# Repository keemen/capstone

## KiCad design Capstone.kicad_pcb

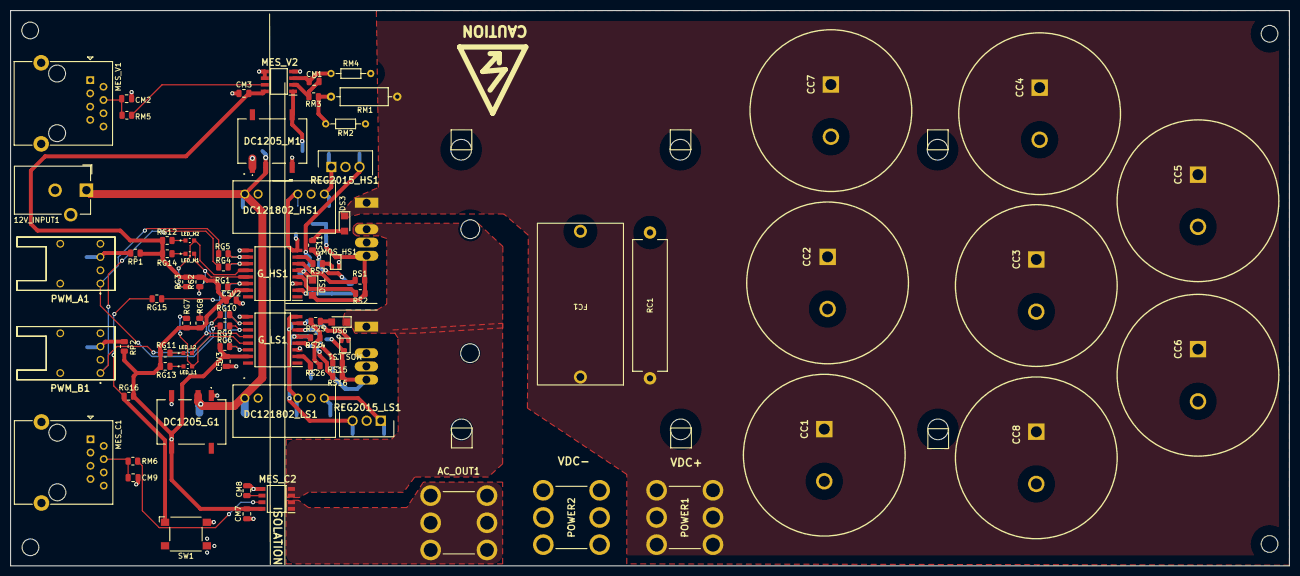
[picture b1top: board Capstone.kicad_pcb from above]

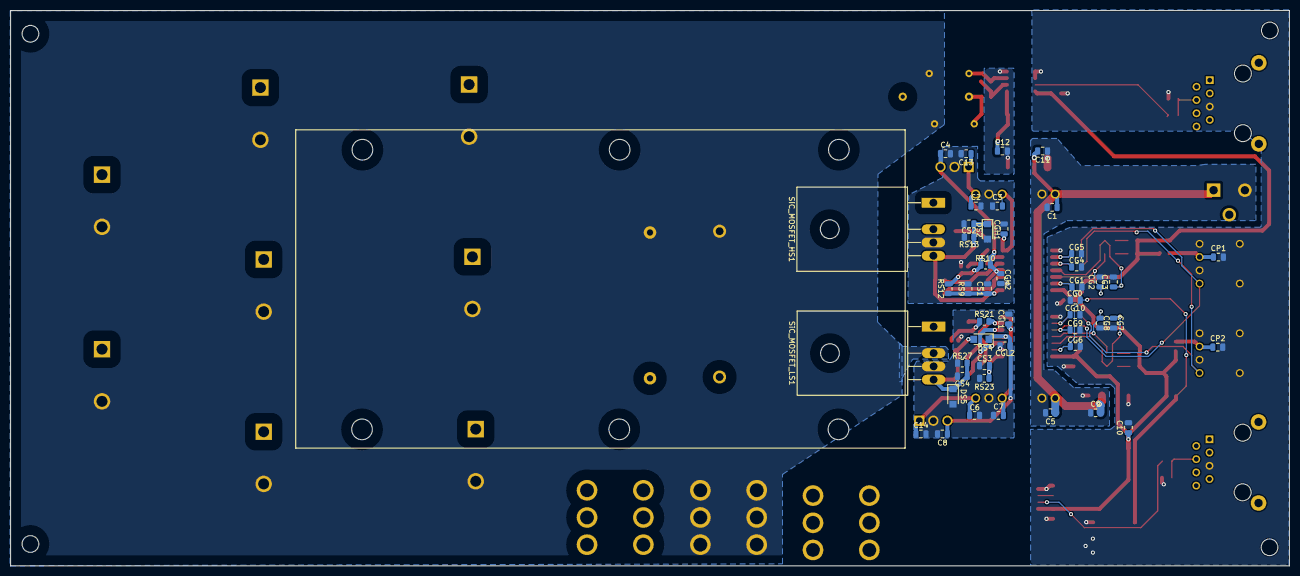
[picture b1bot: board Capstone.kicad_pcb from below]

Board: 2 copper layers, 245.1 x 106.4 mm, 126 parts (47 on the bottom side), 60 nets.

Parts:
12V_INPUT1: Barrel_Jack_FC681465P; BarrelJack_CUI_PJ-102AH_Horizontal
AC_OUT1: 8196
C1, C2, C3, C5, C6, C7, C10, C12: 10uF; C_0805_2012Metric
C4, C8: 0.1uF; C_0805_2012Metric
C5V2, C5V3: 100nF; C_0805_2012Metric
C9, C11: 2.2uF; C_0805_2012Metric
C13, C14: 0.33uF; C_0805_2012Metric
CC1, CC2, CC3, CC4, CC5, CC6, CC7, CC8: 381LX; CAPPRD1000W190D3100H3700
CG0: 16nF; C_0805_2012Metric
CG1, CG2, CG3, CG4, CG5, CG6, CG7, CG8, CG9, CG10: 100pF; C_0805_2012Metric
CGH1, CGH2: 10uF; C_0805_2012Metric
CGL1, CGL2: 10uF; C_0805_2012Metric
CM1: 10nF; C_0805_2012Metric
CM2: 40pF; C_0805_2012Metric
CM3: 100nF; C_0805_2012Metric
CM7: 1uF; C_0805_2012Metric
CM8: 1nF; C_0805_2012Metric
CM9: 100pF; C_0805_2012Metric
CP1, CP2: 0.1uF; C_0805_2012Metric
CS1, CS3: 55pF; C_0805_2012Metric
CS2, CS4: 4.7nF; C_0805_2012Metric
DC1205_G1, DC1205_M1: PDSE2-S24-S24-M; PDSE2S24S24M
DC121802_HS1, DC121802_LS1: MGJ2D121802SC; MGJ2D_7-PIN-SIP
DS1, DS2: SD; D_SMF
DS3, DS4, DS5, DS6: D; D_SMF
FC1: 106MMR250K
G_HS1: UCC21732DW; SOIC127P1030X265-16N
G_LS1: UCC21732DW; SOIC127P1030X265-16N
LED_H1, LED_H2: LED; LED_SML-D12V1WT86
LED_L1, LED_L2: LED; LED_SML-D12V1WT86
MES_C1: RJ45; RJ45_Ninigi_GE
MES_C2: ACHS-7124-000E
MES_V1: RJ45; RJ45_Ninigi_GE
MES_V2: SI8921BB-IS; SI8921
MOS_HS1: 2N7002KW-AU
MOS_LS1: 2N7002KW-AU
POWER1, POWER2: 8196
PWM_A1: AFBR-1528CZ; AFBR1528CZ
PWM_B1: AFBR-1528CZ; AFBR1528CZ
RC1: 20k; R_Axial_Power_L25.0mm_W6.4mm_P27.94mm
REG2015_HS1, REG2015_LS1: L78M15ABV; TO270P460X1020X2008-3P
RG1, RG2, RG3, RG6, RG7, RG8: 10k; R_0805_2012Metric
RG4, RG5, RG9, RG10, RG15: 100; R_0805_2012Metric
RG11, RG12, RG13, RG14: 200; R_0805_2012Metric
RG16: 5k; R_0805_2012Metric
RM1: 100k; R_Axial_DIN0309_L9.0mm_D3.2mm_P12.70mm_Horizontal
RM2, RM4: 20; R_Axial_DIN0204_L3.6mm_D1.6mm_P7.62mm_Horizontal
RM3: 20; R_0805_2012Metric
RM5: 10k; R_0805_2012Metric
RM6: 100; R_0805_2012Metric
RP1, RP2: 2.7; R_0805_2012Metric
RS1, RS2, RS15, RS16: 4.7; R_0805_2012Metric
RS7, RS21: 2; R_0805_2012Metric
RS9, RS23: 732; R_0805_2012Metric
RS10, RS24: 11.8k; R_0805_2012Metric
RS11, RS25: 33; R_0805_2012Metric
RS12, RS26: 3k; R_0805_2012Metric
RS13, RS27: 5k; R_0805_2012Metric
SW1: SW_Push; SW_SPST_Omron_B3FS-105xP
SiC_MOSFET_HS1: C3M0120065K; TO-247-4_Horizontal_TabUp
SiC_MOSFET_LS1: C3M0120065K; TO-247-4_Horizontal_TabUp

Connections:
/Gate_driver/5V_DC: C5V2.1, C5V3.1, C10.1, CM3.2, CM7.2, DC1205_G1.5 (+VO), G_HS1.15 (VCC), G_LS1.15 (VCC), MES_C2.8 (VDD), MES_V2.8 (VDDB), RG1.2, RG2.2, RG3.2, RG6.2, RG7.2, RG8.2, RG11.1, RG12.1, RG13.1, RG14.1, RG16.2, RP1.1, RP2.1
/Gate_driver/-2.5VDC_HS: C3.2, CGH1.1, DC121802_HS1.5 (-VOUT), G_HS1.8 (VEE)
/Gate_driver/-2.5VDC_LS: C7.2, CGL1.1, DC121802_LS1.5 (-VOUT), G_LS1.8 (VEE)
/Gate_driver/CLMPE_HS: G_HS1.7 (CLMPE), RS7.2
/Gate_driver/CLMPE_LS: G_LS1.7 (CLMPE), RS21.2
/Gate_driver/FLT_HS: CG2.1, G_HS1.13 (~FLT), LED_H1.1 (K), RG2.1
/Gate_driver/FLT_LS: CG7.1, G_LS1.13 (~FLT), LED_L1.1 (K), RG7.1
/Gate_driver/GND5V_G: C5V2.2, C5V3.2, C10.2, CG0.2, CG1.2, CG2.2, CG3.2, CG4.2, CG5.2, CG6.2, CG7.2, CG8.2, CG9.2, CG10.2, CM2.2, CM3.1, CM7.1, CM8.1, CM9.1, CP1.2, CP2.2, DC1205_G1.4 (0V), G_HS1.9 (GND), G_LS1.9 (GND), MES_C1.5, MES_C2.5 (GND), MES_V1.5, MES_V2.5 (GNDB), MES_V2.6 (AON), PWM_A1.2 (K), PWM_A1.4 (PIN_2), PWM_A1.5 (HOUSING_PIN_1), PWM_A1.8 (HOUSING_PIN_2), PWM_B1.2 (K), PWM_B1.4 (PIN_2), PWM_B1.5 (HOUSING_PIN_1), PWM_B1.8 (HOUSING_PIN_2), SW1.2
/Gate_driver/OC_HS: CS1.1, G_HS1.2 (OC), RS9.1, RS12.2
/Gate_driver/OC_LS: CS3.1, G_LS1.2 (OC), RS23.1, RS26.2
/Gate_driver/OUTH_HS: G_HS1.4 (OUTH), RS2.2
/Gate_driver/OUTH_LS: G_LS1.4 (OUTH), RS16.2
/Gate_driver/OUTL_HS: G_HS1.6 (OUTL), RS1.2
/Gate_driver/OUTL_LS: G_LS1.6 (OUTL), RS15.2
/Gate_driver/PWM_A: PWM_A1.1 (A), RG5.2, RG9.2
/Gate_driver/PWM_B: PWM_B1.1 (A), RG4.2, RG10.2
/Gate_driver/RDY_HS: CG3.1, G_HS1.12 (RDY), LED_H2.1 (K), RG3.1
/Gate_driver/RDY_LS: CG8.1, G_LS1.12 (RDY), LED_L2.1 (K), RG8.1
/Gate_driver/RST_HS: CG0.1, CG1.1, CG6.1, G_HS1.14 (~RST/EN), G_LS1.14 (~RST/EN), RG1.1, RG6.1, RG15.1
/Gate_driver/VDD_HS: C4.1, CGH2.1, DS1.1 (K), G_HS1.5 (VDD), REG2015_HS1.3 (OUT), RS10.2
/Gate_driver/VDD_LS: C8.1, CGL2.1, DS4.1 (K), G_LS1.5 (VDD), REG2015_LS1.3 (OUT), RS24.2
/Measurement/5VDC_M: C12.1, DC1205_M1.5 (+VO), MES_V2.1 (VDDA)
/Measurement/AC_OUT: AC_OUT1.1, AC_OUT1.2, AC_OUT1.3, AC_OUT1.4, AC_OUT1.5, AC_OUT1.6, MES_C2.1 (IP+_1), MES_C2.2 (IP+_2)
/Measurement/AC_PIN: DS6.1 (K), MES_C2.3 (IP-_1), MES_C2.4 (IP-_2), SiC_MOSFET_HS1.2 (POWER_SOURCE), SiC_MOSFET_LS1.1 (DRAIN)
/Measurement/GND5V_M: C12.2, DC1205_M1.4 (0V), MES_V2.4 (GNDA)
/Measurement/MES_C: CM9.2, MES_C1.4, RM6.1
/Measurement/MES_VP: CM2.1, MES_V1.4, RM5.1
/Measurement/VDC+: CC1.1, CC2.1, CC3.1, CC4.1, CC5.1, CC6.1, CC7.1, CC8.1, DS3.1 (K), FC1.1, POWER1.1, POWER1.2, POWER1.3, POWER1.4, POWER1.5, POWER1.6, RC1.1, RM1.1, SiC_MOSFET_HS1.1 (DRAIN)
/Measurement/VDC-: CC1.2, CC2.2, CC3.2, CC4.2, CC5.2, CC6.2, CC7.2, CC8.2, FC1.2, POWER2.1, POWER2.2, POWER2.3, POWER2.4, POWER2.5, POWER2.6, RC1.2, RM2.2, RM4.2, SiC_MOSFET_LS1.2 (POWER_SOURCE)
/Power/12VDC: 12V_INPUT1.1, C1.1, C5.1, C9.2, C11.2, DC1205_G1.2 (VIN), DC1205_M1.2 (VIN), DC121802_HS1.1 (+VIN), DC121802_LS1.1 (+VIN)
/Power/18VDC_HS: C2.1, C13.1, DC121802_HS1.7 (+VOUT), REG2015_HS1.1 (IN)
/Power/18VDC_LS: C6.1, C14.1, DC121802_LS1.7 (+VOUT), REG2015_LS1.1 (IN)
/Power/GND12: 12V_INPUT1.2, C1.2, C5.2, C9.1, C11.1, DC1205_G1.1 (GND), DC1205_M1.1 (GND), DC121802_HS1.2 (-VIN), DC121802_LS1.2 (-VIN)
/Power/GND_H_HS: C2.2, C3.1, C4.2, C13.2, CGH1.2, CGH2.2, CS1.2, CS2.2, DC121802_HS1.6 (0V), DS2.2 (A), G_HS1.3 (COM), MOS_HS1.2 (S), REG2015_HS1.2 (GND), RS9.2, RS13.2, SiC_MOSFET_HS1.3 (DRIVER_SOURCE)
/Power/GND_H_LS: C6.2, C7.1, C8.2, C14.2, CGL1.2, CGL2.2, CS3.2, CS4.2, DC121802_LS1.6 (0V), DS5.2 (A), G_LS1.3 (COM), MOS_LS1.2 (S), REG2015_LS1.2 (GND), RS23.2, RS27.2, SiC_MOSFET_LS1.3 (DRIVER_SOURCE)
unnamed: CG4.1, G_HS1.11 (IN-), RG4.1
unnamed: CG5.1, G_HS1.10 (IN+), RG5.1
unnamed: CG9.1, G_LS1.11 (IN-), RG9.1
unnamed: CG10.1, G_LS1.10 (IN+), RG10.1
unnamed: CM1.1, MES_V2.2 (AIP), RM3.1
unnamed: CM1.2, MES_V2.3 (AIN), RM4.1
unnamed: CM8.2, MES_C2.6 (FILTER)
unnamed: CP1.1, PWM_A1.3 (PIN_1), RP1.2
unnamed: CS2.1, DS1.2 (A), DS2.1 (K), MOS_HS1.3 (D), RS1.1, RS2.1, RS13.1, SiC_MOSFET_HS1.4 (GATE)
unnamed: CS4.1, DS4.2 (A), DS5.1 (K), MOS_LS1.3 (D), RS15.1, RS16.1, RS27.1, SiC_MOSFET_LS1.4 (GATE)
unnamed: DS3.2 (A), RS11.1
unnamed: DS6.2 (A), RS25.1
unnamed: LED_H1.2 (A), RG14.2
unnamed: LED_H2.2 (A), RG12.2
unnamed: LED_L1.2 (A), RG13.2
unnamed: LED_L2.2 (A), RG11.2
unnamed: MES_V2.7 (AOP), RM5.2
unnamed: MOS_HS1.1 (G), RS7.1
unnamed: MOS_LS1.1 (G), RS21.1
unnamed: CP2.1, PWM_B1.3 (PIN_1), RP2.2
unnamed: RG15.2, RG16.1, SW1.1
unnamed: RM1.2, RM2.1, RM3.2
unnamed: MES_C2.7 (VOUT), RM6.2
unnamed: RS10.1, RS11.2, RS12.1
unnamed: RS24.1, RS25.2, RS26.1
